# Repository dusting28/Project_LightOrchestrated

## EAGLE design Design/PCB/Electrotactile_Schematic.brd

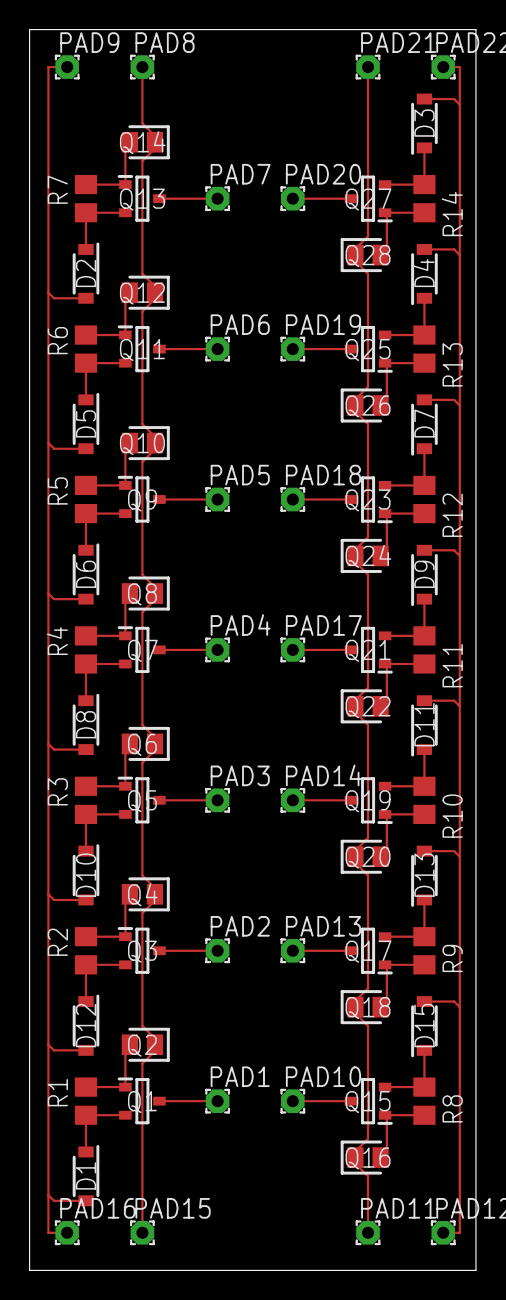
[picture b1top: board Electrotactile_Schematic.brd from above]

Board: 2 copper layers, 30.1 x 83.8 mm, 78 parts (0 on the bottom side), 46 nets.

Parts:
D1, D2, D3, D4, D5, D6, D7, D8, D9, D10, D11, D12, D13, D15: S-202T; SODFL3516X70N
PAD1, PAD2, PAD3, PAD4, PAD5, PAD6, PAD7, PAD8, PAD9, PAD10, PAD11, PAD12, PAD13, PAD14, PAD15, PAD16, PAD17, PAD18, PAD19, PAD20, PAD21, PAD22: 0; 1,6/0,8
Q1, Q3, Q5, Q7, Q9, Q11, Q13, Q15, Q17, Q19, Q21, Q23, Q25, Q27: CMPTA94_TR_PBFREE; SOT95P230X109-3N
Q2, Q4, Q6, Q8, Q10, Q12, Q14, Q16, Q18, Q20, Q22, Q24, Q26, Q28: TEMT6200FX01; LEDC2012X95N
R1, R2, R3, R4, R5, R6, R7, R8, R9, R10, R11, R12, R13, R14: 22k; R0805

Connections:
unnamed: Q15.1, Q16.2, R8.2
unnamed: D3.1, Q27.2, R14.1
unnamed: Q1.1, Q2.2, R1.2
unnamed: PAD1.1, Q1.3
unnamed: Q3.1, Q4.2, R2.2
unnamed: PAD2.1, Q3.3
unnamed: D6.1, Q9.2, R5.1
unnamed: PAD10.1, Q15.3
unnamed: D3.2, D4.2, D7.2, D9.2, D11.2, D13.2, D15.2, PAD12.1, PAD22.1
unnamed: PAD8.1, PAD15.1, Q2.1, Q4.1, Q6.1, Q8.1, Q10.1, Q12.1, Q14.1
unnamed: Q5.1, Q6.2, R3.2
unnamed: PAD3.1, Q5.3
unnamed: D10.1, Q5.2, R3.1
unnamed: Q17.1, Q18.2, R9.2
unnamed: PAD13.1, Q17.3
unnamed: Q7.1, Q8.2, R4.2
unnamed: PAD4.1, Q7.3
unnamed: D5.1, Q11.2, R6.1
unnamed: PAD11.1, PAD21.1, Q16.1, Q18.1, Q20.1, Q22.1, Q24.1, Q26.1, Q28.1
unnamed: Q9.1, Q10.2, R5.2
unnamed: PAD5.1, Q9.3
unnamed: D8.1, Q7.2, R4.1
unnamed: Q19.1, Q20.2, R10.2
unnamed: PAD14.1, Q19.3
unnamed: Q11.1, Q12.2, R6.2
unnamed: PAD6.1, Q11.3
unnamed: D1.1, Q1.2, R1.1
unnamed: D13.1, Q17.2, R9.1
unnamed: Q21.1, Q22.2, R11.2
unnamed: Q13.1, Q14.2, R7.2
unnamed: PAD7.1, Q13.3
unnamed: D2.1, Q13.2, R7.1
unnamed: D1.2, D2.2, D5.2, D6.2, D8.2, D10.2, D12.2, PAD9.1, PAD16.1
unnamed: PAD17.1, Q21.3
unnamed: D11.1, Q19.2, R10.1
unnamed: Q23.1, Q24.2, R12.2
unnamed: PAD18.1, Q23.3
unnamed: D9.1, Q21.2, R11.1
unnamed: Q25.1, Q26.2, R13.2
unnamed: PAD19.1, Q25.3
unnamed: D7.1, Q23.2, R12.1
unnamed: Q27.1, Q28.2, R14.2
unnamed: PAD20.1, Q27.3
unnamed: D4.1, Q25.2, R13.1
unnamed: D15.1, Q15.2, R8.1
unnamed: D12.1, Q3.2, R2.1

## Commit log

2024-11-15 Added Measurement Code
2024-11-15 Added files from lab desktop
2024-11-15 Moved folders around
2024-11-15 Testing github
2024-11-25 Small changes to file architecture
2024-11-25 Small design modifications
2025-01-14 DesignV1
2025-01-27 Version3 of Design
2025-02-03 Dynamics Model of System
2025-02-26 small change
2025-02-26 Added Paul's CAD
2025-02-26 Customized Version Added
2025-02-27 Started PCB Design
2025-03-02 Max patches for thermal stress test
2025-03-02 Edited Version 2 to Mimic Paul Prototype
2025-03-03 Version 2 updated
2025-03-03 temp files removed
2025-03-15 Pulsed Data Collected
2025-03-16 Additional pulsed measurements
2025-03-16 Momentum-Based Version
2025-03-16 Momentum-based analysis
2025-03-19 Updated CAD to Momentum-Based
2025-03-19 Testing Phototransistor
2025-03-24 Shielding analysis with gaps
2025-03-24 kicad pcb
2025-03-24 Moved max patches
2025-03-26 Finished 10x10 design
2025-03-26 Electronics Measurements
2025-03-26 Made drawing for machine shop
2025-03-27 Added silkscreen layer
2025-03-27 Small CAD updates
2025-03-29 Moved CAD around
2025-03-31 Created new engineering drawing for Josh
2025-04-03 PCB design with larger MOSFET
2025-04-05 Edited CAD
2025-04-07 PCB design with new MOSFETs
2025-04-09 Finished 10x10 PCB with new mosfets
2025-04-17 Created figures 1-3 and rendered PCB CAD
2025-04-17 Edited CAD to make 9 mm shielding holes
2025-04-22 Captured Data with LED source
2025-04-24 Compression Test Completed
2025-04-24 Redesigned with Nonlinear Spring
2025-04-26 Restructured Files
2025-05-08 Thermal measurements taken
2025-05-08 More LED control from Arduino
2025-05-20 Updated CAD
2025-05-20 COMSOL EM forces with shielding
2025-05-23 Created light patterns for laptop
2025-05-23 Added 10x10 design for linear guide
2025-05-31 Analyzed Proportional Data
2025-05-31 Gathered pulsed data for proportional control and thermal measurements
2025-06-02 Data for Lab Meeting
2025-06-02 COMSOL Elastic
2025-06-02 Optical Cavity Design
2025-06-02 Minor changes
2025-06-03 Re-aligned positioning holes in PCB design
2025-06-04 Thermal Calibration
2025-06-05 Calibrated thermal measurements
2025-06-18 Finished Dynamic Measurements
    Verify thermal results before moving forward.
2025-06-18 Analyzed Thermal Data
2025-06-18 Took last mechanical measurements
2025-06-25 CAD for Perception Study
2025-06-25 Generated Figures for Dynamic Measurements and Thermal Analysis
2025-06-26 Finished thermal figure
2025-07-04 Modification to troubleshoot device reliability issues
2025-07-07 Finished first pilot study with Cole
2025-07-07 Designs for troubleshooting device
2025-07-10 Finished Perception Study
2025-07-10 Scripts for Analyzing Perception Data
2025-07-11 Updated participant contact info
2025-07-11 Generated subfigures for perception study
2025-07-13 Finished Editing Figures
2025-07-18 Added Moving Line
2025-07-18 Implemented round 1 of Yon feedback
2025-07-18 Output Moving Line
2025-07-25 Magnitude Study + Video Documentation
2025-07-26 Added premiere movies
2025-08-01 Added new metrics for localization
